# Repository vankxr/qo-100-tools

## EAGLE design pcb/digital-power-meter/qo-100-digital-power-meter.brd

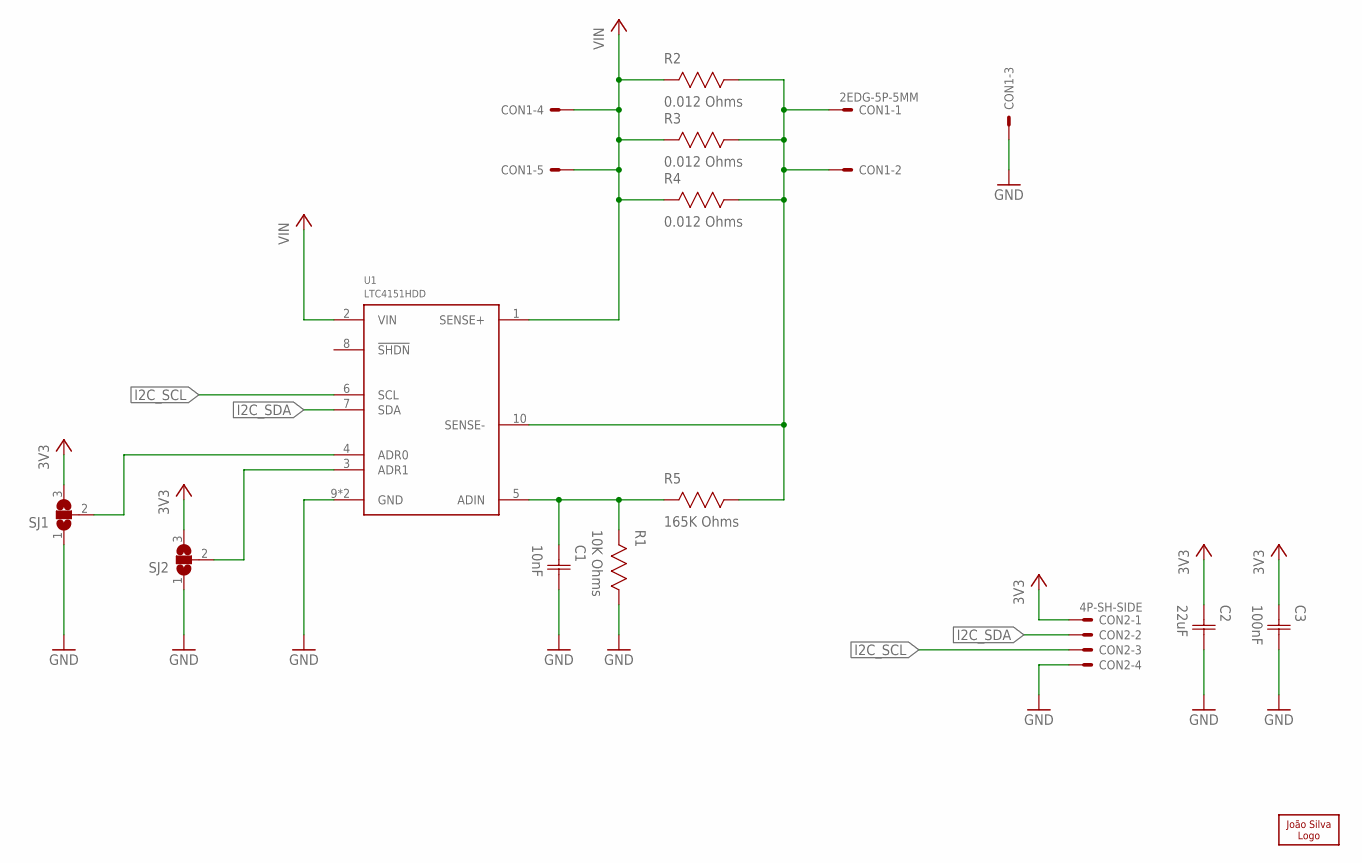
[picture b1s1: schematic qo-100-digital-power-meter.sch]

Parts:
C1: 10nF; CAP0603
C2: 22uF; CAP1206
C3: 100nF; CAP0603
CON1: 2EDG-5P-5MM
CON2: 4P-SH-SIDE; SH-04-SIDE
LOGO1: JS-5MM; JS_5MM
R1: 10K Ohms; RES0603
R2, R3, R4: 0.012 Ohms; RES2512
R5: 165K Ohms; RES0603
SJ1, SJ2: SJ2S; SJ2_S
U1: LTC4151HDD; DFN10

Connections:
3V3: C2.1 (C1), C3.1 (C1), CON2.1, SJ1.3, SJ2.3
GND: C1.2 (C2), C2.2 (C2), C3.2 (C2), CON1.P$3, CON2.4, R1.1, SJ1.1, SJ2.1, U1.9 (GND), U1.11 (GND)
I2C_SCL: CON2.3, U1.6 (SCL)
I2C_SDA: CON2.2, U1.7 (SDA)
unnamed: C1.1 (C1), R1.2, R5.2, U1.5 (ADIN)
unnamed: CON1.P$1, CON1.P$2, R2.1, R3.1, R4.1, R5.1, U1.10 (SENSE-)
unnamed: SJ1.2, U1.4 (ADR0)
unnamed: SJ2.2, U1.3 (ADR1)
VIN: CON1.P$4, CON1.P$5, R2.2, R3.2, R4.2, U1.1 (SENSE+), U1.2 (VIN)

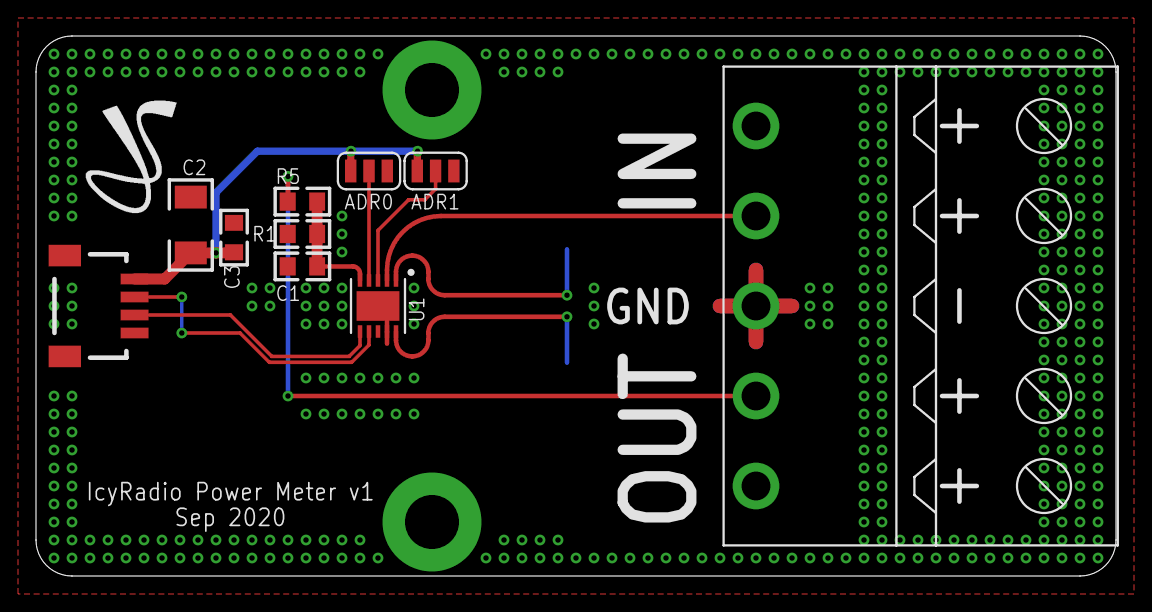
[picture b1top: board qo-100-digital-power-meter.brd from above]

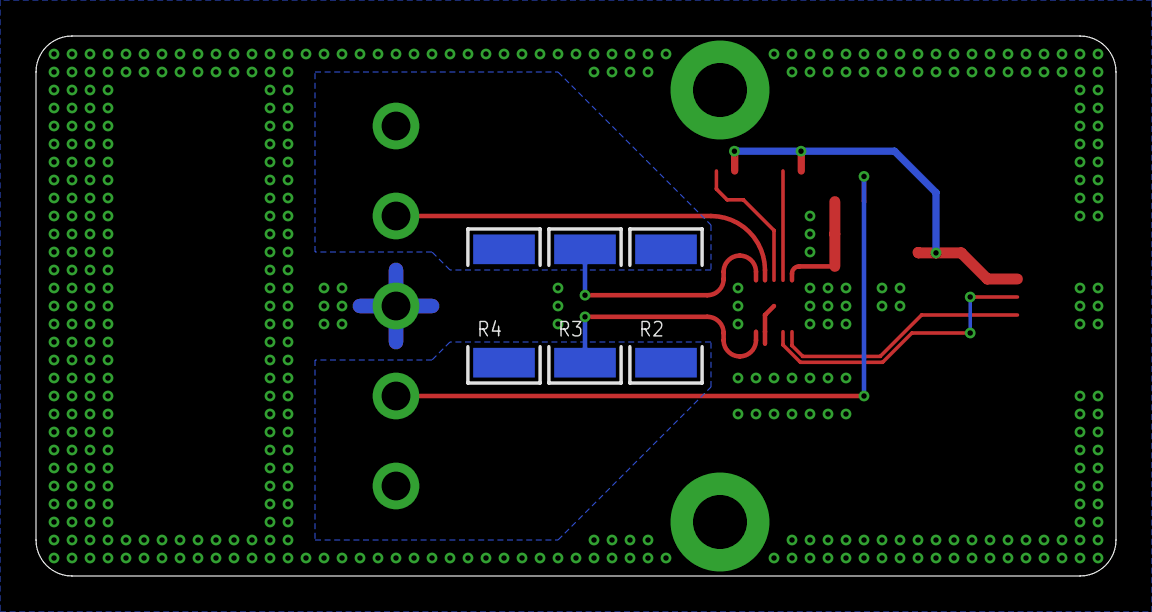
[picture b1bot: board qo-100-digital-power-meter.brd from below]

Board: 2 copper layers, 60.0 x 30.0 mm, 14 parts (3 on the bottom side), 9 nets.

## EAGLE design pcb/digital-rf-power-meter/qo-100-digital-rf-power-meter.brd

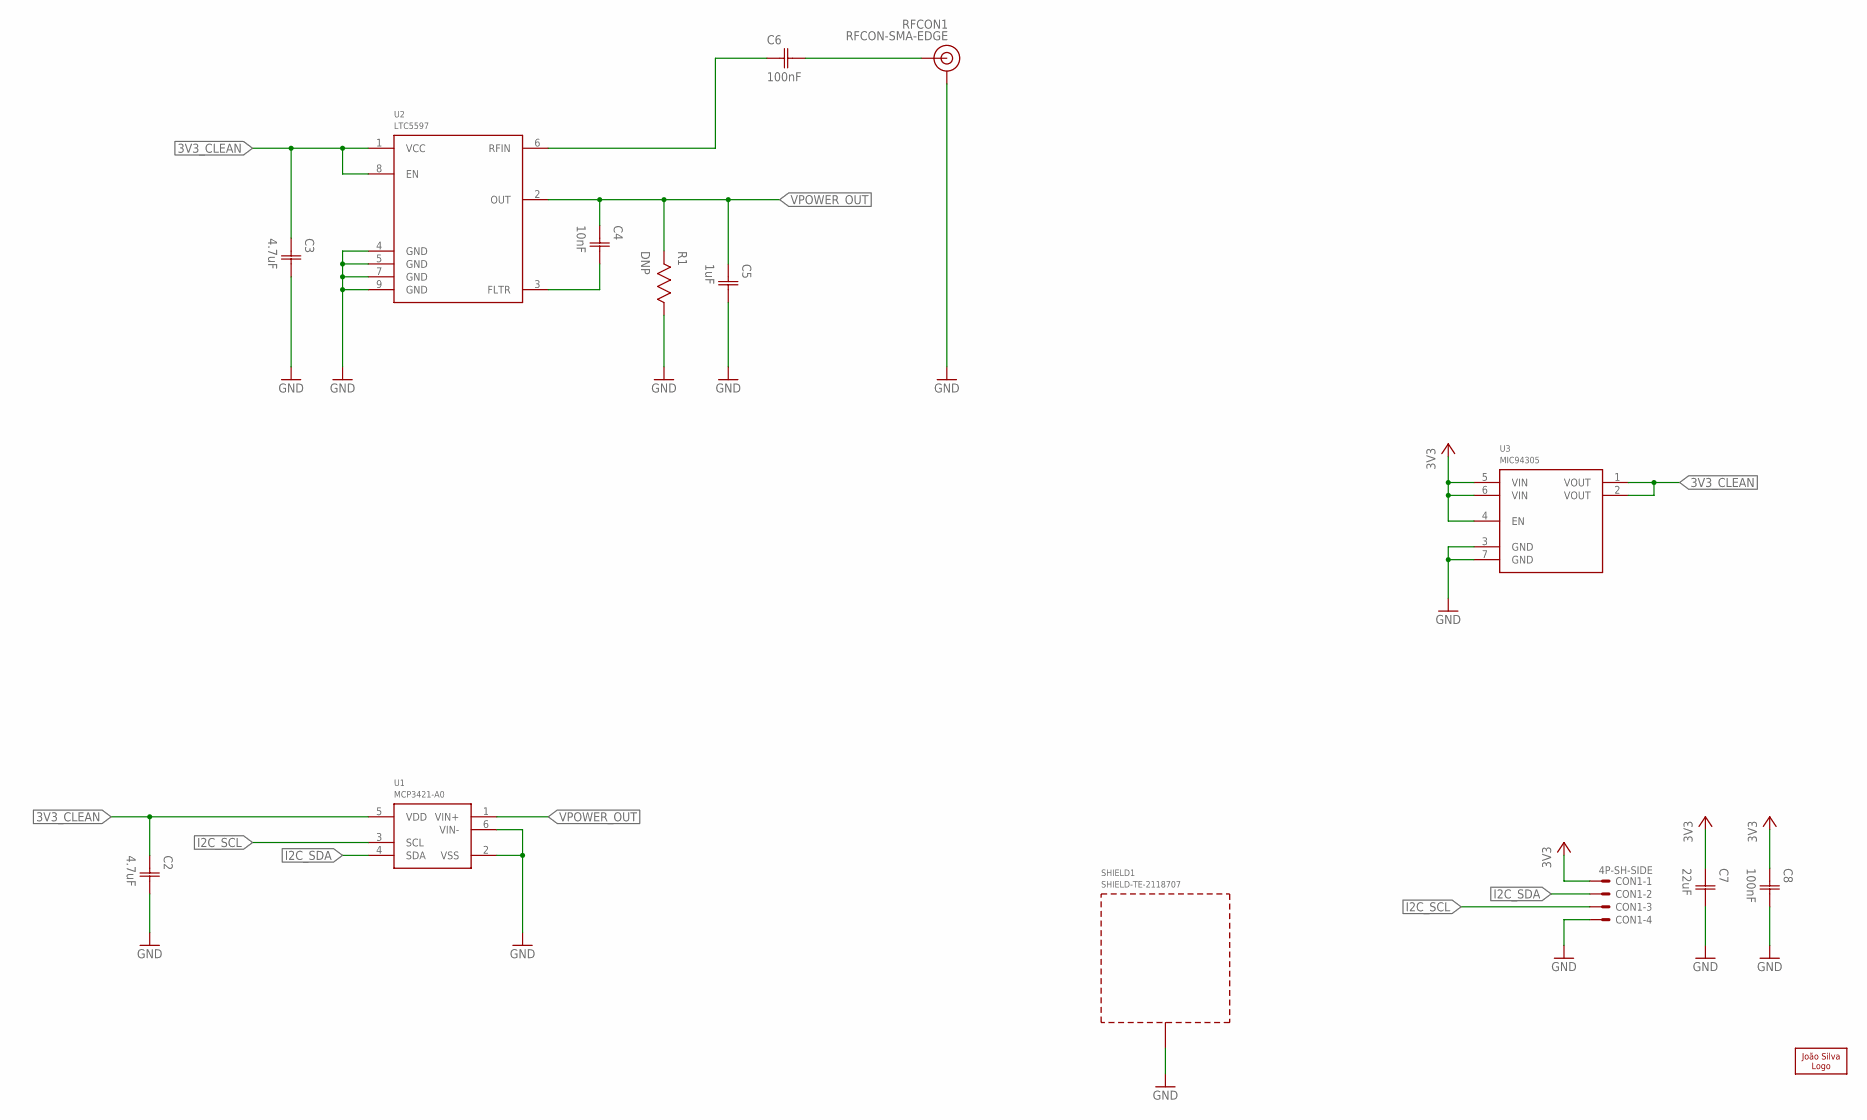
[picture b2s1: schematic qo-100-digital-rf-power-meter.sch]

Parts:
C2, C3: 4.7uF; CAP0603
C4: 10nF; CAP0603
C5: 1uF; CAP0603
C6, C8: 100nF; CAP0603
C7: 22uF; CAP1206
CON1: 4P-SH-SIDE; SH-04-SIDE
LOGO1: JS-5MM; JS_5MM
R1: DNP; RES0603
RFCON1: RFCON-SMA-EDGE; SMA-EDGE
SHIELD1: SHIELD-TE-2118707; 2118707
U1: MCP3421-A0; SOT23-6
U2: LTC5597; DFN8_2X2
U3: MIC94305; DFN6

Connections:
3V3: C7.1 (C1), C8.1 (C1), CON1.1, U3.4 (EN), U3.5 (VIN), U3.6 (VIN)
3V3_CLEAN: C2.1 (C1), C3.1 (C1), U1.5 (VDD), U2.1 (VCC), U2.8 (EN), U3.1 (VOUT), U3.2 (VOUT)
GND: C2.2 (C2), C3.2 (C2), C5.2 (C2), C7.2 (C2), C8.2 (C2), CON1.4, R1.1, RFCON1.GND@0 (GND), RFCON1.GND@1 (GND), RFCON1.GND@2 (GND), RFCON1.GND@3 (GND), SHIELD1.1, SHIELD1.2, SHIELD1.3, SHIELD1.4, SHIELD1.5, SHIELD1.6, SHIELD1.7, SHIELD1.8, SHIELD1.9, SHIELD1.10, SHIELD1.11, SHIELD1.12, U1.2 (VSS), U1.6 (VIN-), U2.4 (GND), U2.5 (GND), U2.7 (GND), U2.9 (GND), U3.3 (GND), U3.7 (GND)
I2C_SCL: CON1.3, U1.3 (SCL)
I2C_SDA: CON1.2, U1.4 (SDA)
unnamed: C6.1 (C1), U2.6 (RFIN)
unnamed: C6.2 (C2), RFCON1.SIG (SIGNAL)
unnamed: C4.2 (C2), U2.3 (FLTR)
VPOWER_OUT: C4.1 (C1), C5.1 (C1), R1.2, U1.1 (VIN+), U2.2 (OUT)

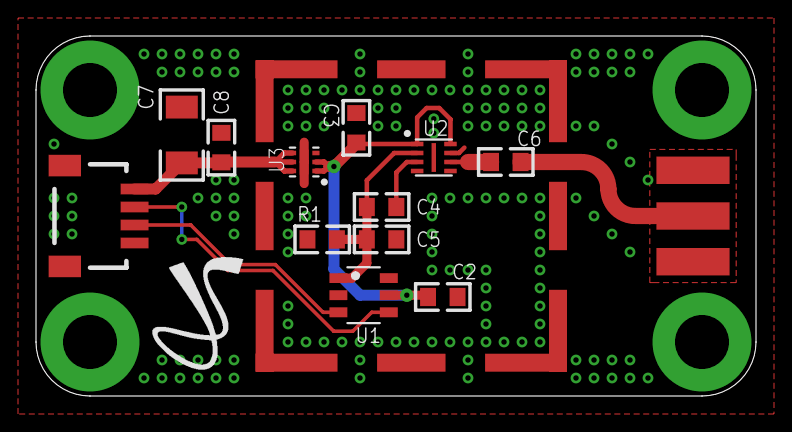
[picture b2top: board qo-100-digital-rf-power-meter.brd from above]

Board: 2 copper layers, 40.0 x 20.0 mm, 15 parts (0 on the bottom side), 9 nets.

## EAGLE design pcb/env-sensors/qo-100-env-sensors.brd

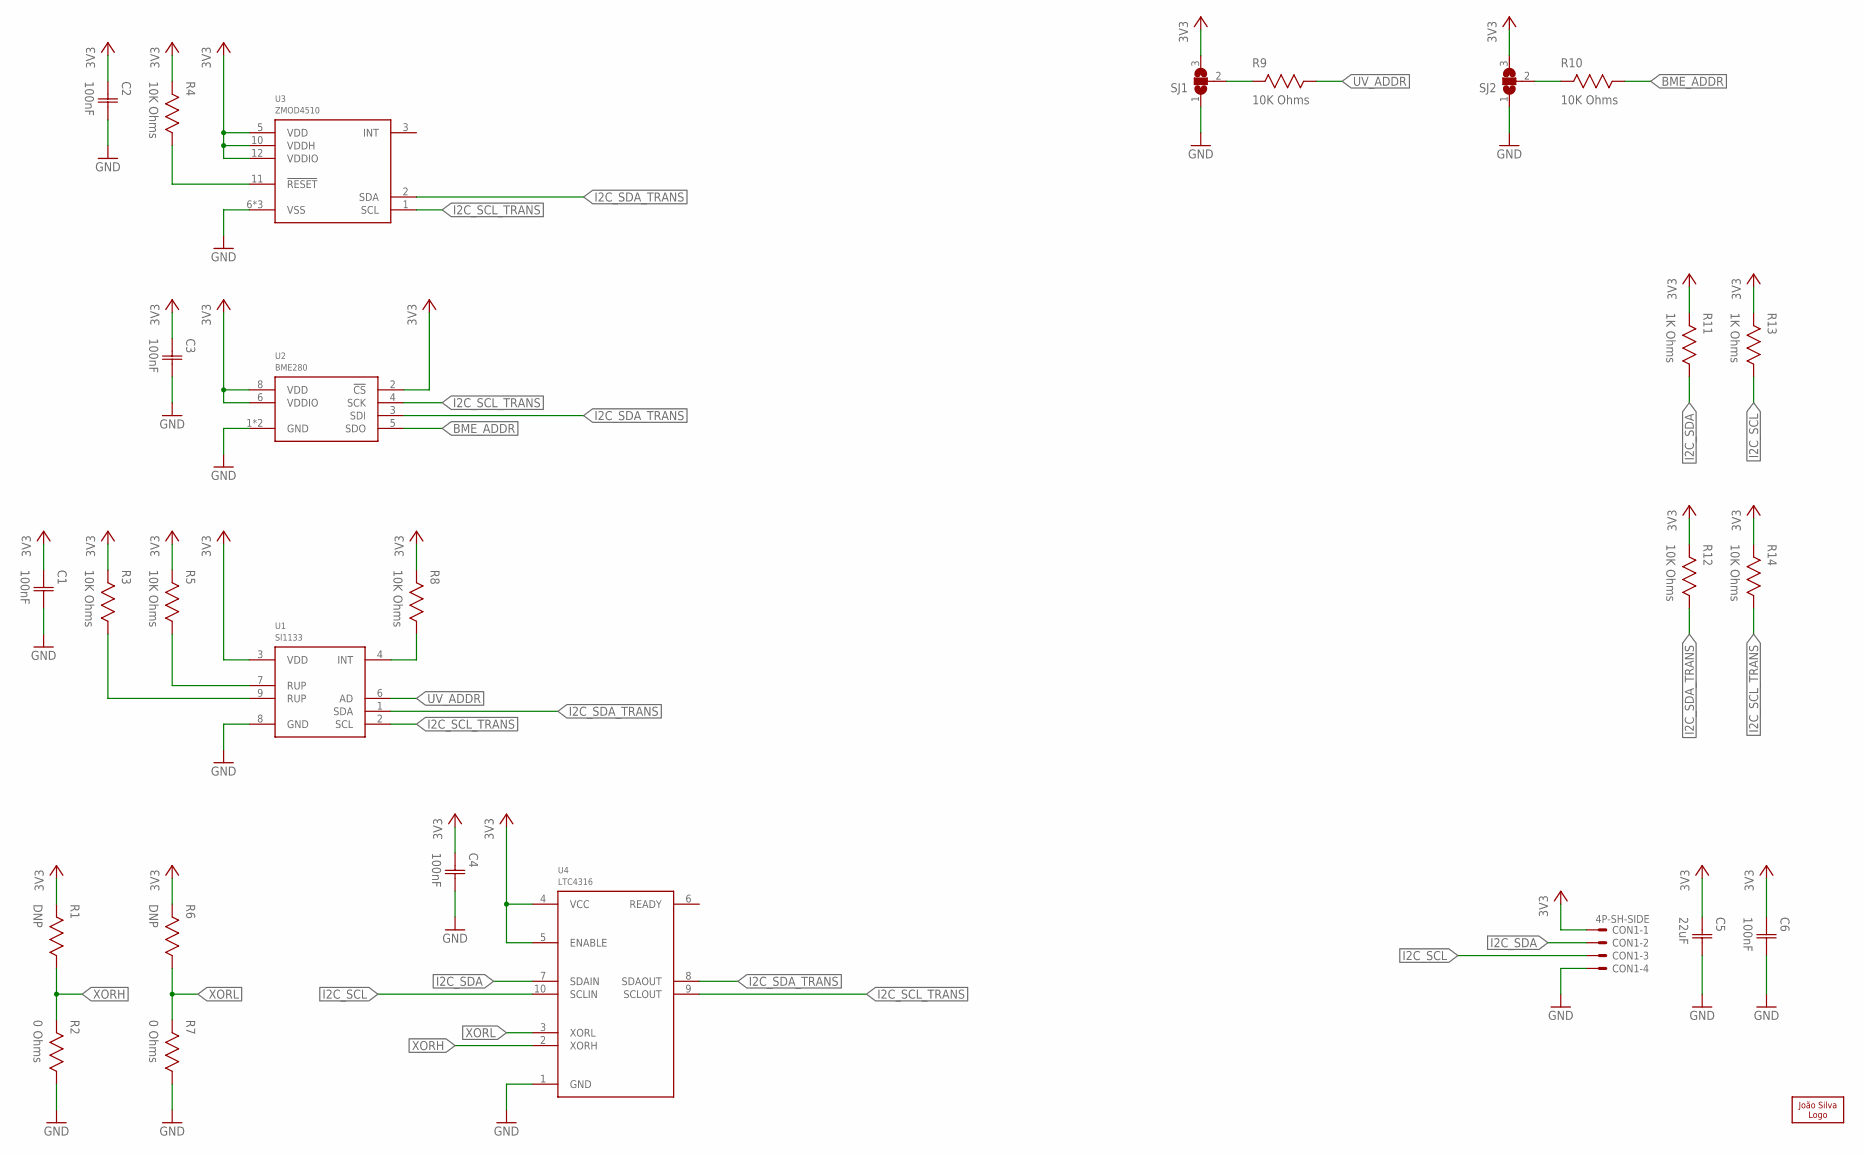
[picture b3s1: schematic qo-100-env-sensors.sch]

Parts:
C1, C2, C3, C4, C6: 100nF; CAP0603
C5: 22uF; CAP1206
CON1: 4P-SH-SIDE; SH-04-SIDE
LOGO1: JS-5MM; JS_5MM
R1, R6: DNP; RES0603
R2, R7: 0 Ohms; RES0603
R3, R4, R5, R8, R9, R10, R12, R14: 10K Ohms; RES0603
R11, R13: 1K Ohms; RES0603
SJ1, SJ2: SJ2S; SJ2_S
U1: SI1133; DFN10
U2: BME280
U3: ZMOD4510; LGA12
U4: LTC4316; MSOP10

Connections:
3V3: C1.1 (C1), C2.1 (C1), C3.1 (C1), C4.1 (C1), C5.1 (C1), C6.1 (C1), CON1.1, R1.2, R3.2, R4.2, R5.2, R6.2, R8.2, R11.2, R12.2, R13.2, R14.2, SJ1.3, SJ2.3, U1.3 (VDD), U2.2 (!CS), U2.6 (VDDIO), U2.8 (VDD), U3.5 (VDD), U3.10 (VDDH), U3.12 (VDDIO), U4.4 (VCC), U4.5 (ENABLE)
BME_ADDR: R10.1, U2.5 (SDO)
GND: C1.2 (C2), C2.2 (C2), C3.2 (C2), C4.2 (C2), C5.2 (C2), C6.2 (C2), CON1.4, R2.1, R7.1, SJ1.1, SJ2.1, U1.8 (GND), U2.1 (GND), U2.7 (GND), U3.6 (VSS), U3.7 (VSS), U3.9 (VSS), U4.1 (GND)
I2C_SCL: CON1.3, R13.1, U4.10 (SCLIN)
I2C_SCL_TRANS: R14.1, U1.2 (SCL), U2.4 (SCK), U3.1 (SCL), U4.9 (SCLOUT)
I2C_SDA: CON1.2, R11.1, U4.7 (SDAIN)
I2C_SDA_TRANS: R12.1, U1.1 (SDA), U2.3 (SDI), U3.2 (SDA), U4.8 (SDAOUT)
unnamed: R4.1, U3.11 (!RESET)
unnamed: R3.1, U1.9 (RUP)
unnamed: R8.1, U1.4 (INT)
unnamed: R10.2, SJ2.2
unnamed: R9.2, SJ1.2
unnamed: R5.1, U1.7 (RUP)
UV_ADDR: R9.1, U1.6 (AD)
XORH: R1.1, R2.2, U4.2 (XORH)
XORL: R6.1, R7.2, U4.3 (XORL)

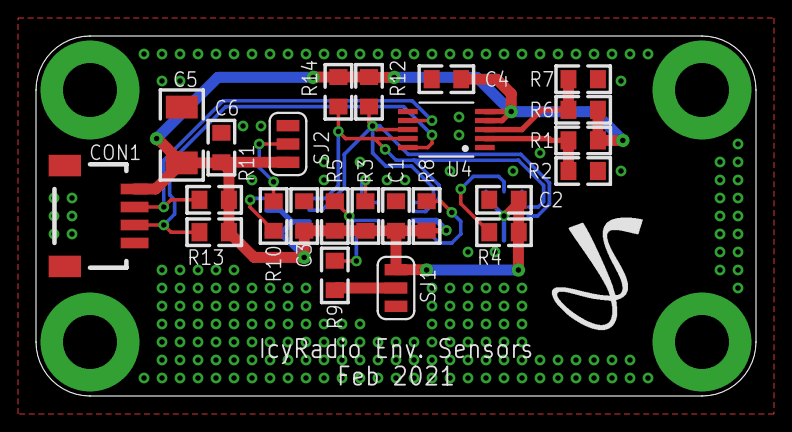
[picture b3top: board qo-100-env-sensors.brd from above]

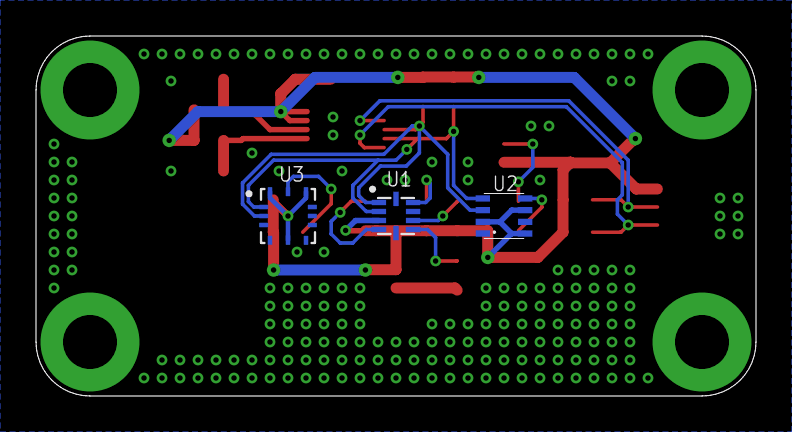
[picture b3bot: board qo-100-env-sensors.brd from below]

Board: 2 copper layers, 40.0 x 20.0 mm, 28 parts (3 on the bottom side), 16 nets.

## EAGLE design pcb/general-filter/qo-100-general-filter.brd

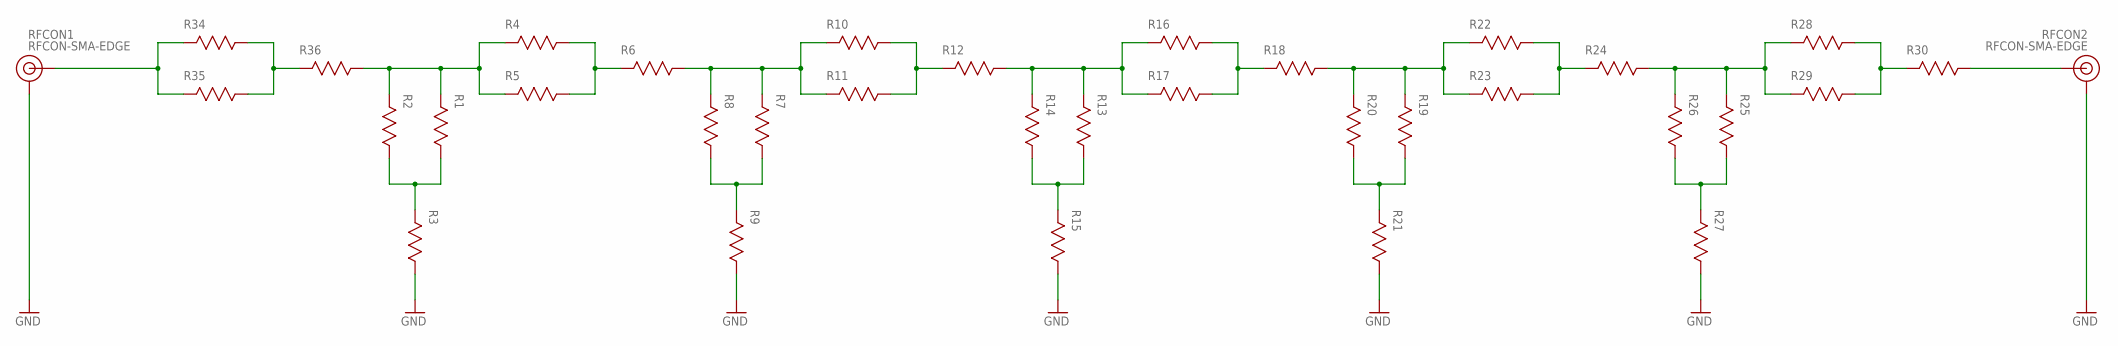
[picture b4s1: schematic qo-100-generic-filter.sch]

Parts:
R1, R2, R3, R4, R5, R6, R7, R8, R9, R10, R11, R12, R13, R14, R15, R16, R17, R18, R19, R20, R21, R22, R23, R24, R25, R26, R27, R28, R29, R30, R34, R35, R36: RESISTOR-0603; RES0603
RFCON1, RFCON2: RFCON-SMA-EDGE; SMA-EDGE

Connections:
GND: R3.1, R9.1, R15.1, R21.1, R27.1, RFCON1.GND@0 (GND), RFCON1.GND@1 (GND), RFCON1.GND@2 (GND), RFCON1.GND@3 (GND), RFCON2.GND@0 (GND), RFCON2.GND@1 (GND), RFCON2.GND@2 (GND), RFCON2.GND@3 (GND)
unnamed: R1.2, R2.2, R4.2, R5.2, R36.1
unnamed: R1.1, R2.1, R3.2
unnamed: R6.1, R7.2, R8.2, R10.2, R11.2
unnamed: R4.1, R5.1, R6.2
unnamed: R7.1, R8.1, R9.2
unnamed: R10.1, R11.1, R12.2
unnamed: R12.1, R13.2, R14.2, R16.2, R17.2
unnamed: R13.1, R14.1, R15.2
unnamed: R16.1, R17.1, R18.2
unnamed: R18.1, R19.2, R20.2, R22.2, R23.2
unnamed: R19.1, R20.1, R21.2
unnamed: R22.1, R23.1, R24.2
unnamed: R24.1, R25.2, R26.2, R28.2, R29.2
unnamed: R25.1, R26.1, R27.2
unnamed: R28.1, R29.1, R30.2
unnamed: R30.1, RFCON2.SIG (SIGNAL)
unnamed: R34.2, R35.2, RFCON1.SIG (SIGNAL)
unnamed: R34.1, R35.1, R36.2

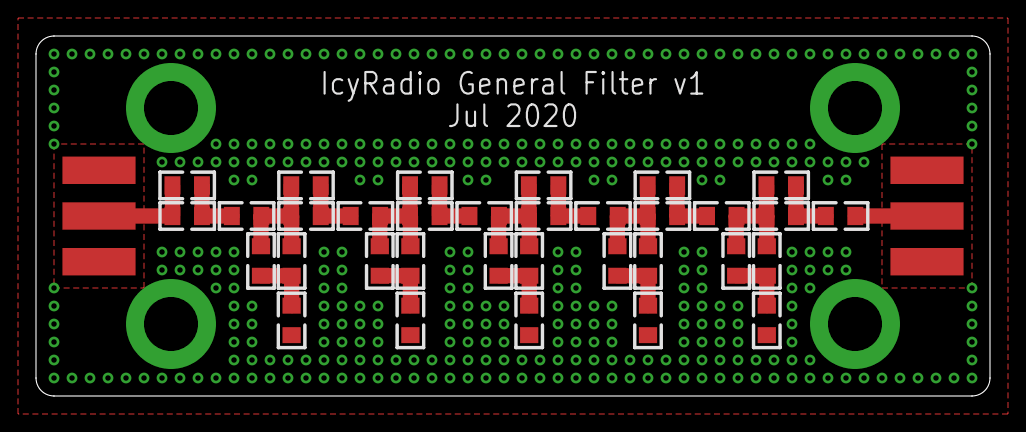
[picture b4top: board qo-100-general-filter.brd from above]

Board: 2 copper layers, 53.0 x 20.0 mm, 35 parts (0 on the bottom side), 19 nets.
